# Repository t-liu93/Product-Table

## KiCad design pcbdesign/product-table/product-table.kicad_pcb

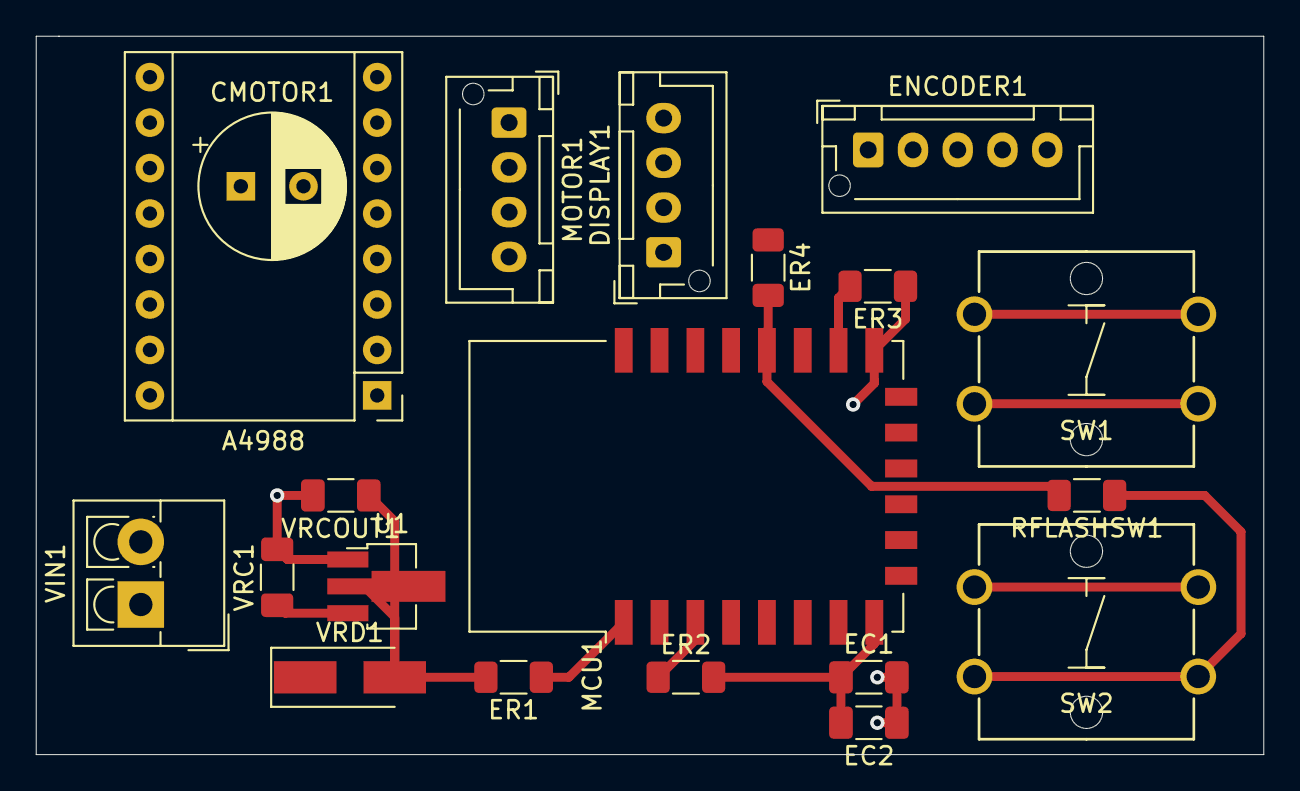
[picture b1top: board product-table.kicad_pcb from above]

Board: 2 copper layers, 68.6 x 40.1 mm, 20 parts (0 on the bottom side), 19 nets.

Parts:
A4988: Pololu_Breakout_A4988; Pololu_Breakout-16_15.2x20.3mm
CMOTOR1: 100uF; CP_Radial_D8.0mm_P3.50mm
DISPLAY1: Conn_01x04; JST_XH_B4B-XH-AM_1x04_P2.50mm_Vertical
EC1: 10uF; C_1206_3216Metric_Pad1.33x1.80mm_HandSolder
EC2: 100nF; C_1206_3216Metric_Pad1.33x1.80mm_HandSolder
ENCODER1: Conn_01x05; JST_XH_B5B-XH-AM_1x05_P2.50mm_Vertical
ER1, ER2, ER3, ER4: 10K; R_1206_3216Metric_Pad1.30x1.75mm_HandSolder
MCU1: ESP-12F; ESP-12E
MOTOR1: Conn_01x04; JST_XH_B4B-XH-AM_1x04_P2.50mm_Vertical
RFLASHSW1: 100; R_1206_3216Metric_Pad1.30x1.75mm_HandSolder
SW1, SW2: Omron-B3F-4055; SW_PUSH_Omron_B3F-4055
U1: LM1117-3.3; SOT-89-3_Handsoldering
VIN1: Terminal; TerminalBlock_4Ucon_1x02_P3.50mm_Vertical
VRC1: 10uF; C_1206_3216Metric_Pad1.33x1.80mm_HandSolder
VRCOUT1: 10uF; C_1206_3216Metric_Pad1.33x1.80mm_HandSolder
VRD1: D_Schottky; D_SMA_Handsoldering

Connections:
+3V3: A4988.2, A4988.10, A4988.11, A4988.12, DISPLAY1.1, EC1.1, EC2.2, ENCODER1.2, ER1.2, ER2.2, ER4.1, MCU1.8, U1.2, VRCOUT1.1, VRD1.2
+12V: A4988.8, CMOTOR1.1, U1.3, VIN1.1, VRC1.1, VRD1.1
/GPIO0: A4988.15, ER4.2, MCU1.18, RFLASHSW1.2
/GPIO2: A4988.16, MCU1.17
/GPIO4: DISPLAY1.4, MCU1.19
/GPIO5: DISPLAY1.3, MCU1.20
/GPIO12: ENCODER1.4, MCU1.6
/GPIO13: ENCODER1.5, MCU1.7
/GPIO14: ENCODER1.3, MCU1.5
/esp8266/EN: ER2.1, MCU1.3
/esp8266/GPIO15: ER3.2, MCU1.16
/esp8266/RST: ER1.1, MCU1.1, SW1.3, SW1.4
GND: A4988.1, A4988.7, A4988.9, CMOTOR1.2, DISPLAY1.2, EC1.2, EC2.1, ENCODER1.1, ER3.1, MCU1.15, SW1.1, SW1.2, SW2.3, SW2.4, U1.1, VIN1.2, VRC1.2, VRCOUT1.2
unnamed: A4988.3, MOTOR1.1
unnamed: A4988.4, MOTOR1.2
unnamed: A4988.5, MOTOR1.3
unnamed: A4988.6, MOTOR1.4
unnamed: A4988.13, A4988.14
unnamed: RFLASHSW1.1, SW2.1, SW2.2

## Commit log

2020-06-04 Initialize submodules
2020-06-04 Initialize Makefile
2020-06-04 Add .gitignore
2020-10-11 Bump Arduino 2.7.4
2020-10-11 Remove submodule to change location
2020-10-11 Add submodule Arduino and makefile
2020-10-11 Add submodule ota
2020-10-11 Add timer class
2020-10-11 Remove
2020-10-11 New sub
2020-10-11 Update purge submodules
2020-10-11 Start with it
2020-10-12 Add u8g2
2020-10-14 Add stepper driver library
2020-10-23 Add submodule
2020-10-23 Add PCB design
2020-10-23 commit pcb
2020-10-23 Bump esp
2020-10-24 Remove cache of backup files
2020-10-24 Remove some no needed files
2020-10-24 Update gitignore with necessary kicad info
2020-10-24 Bump ota
2020-10-24 Remove ota submodule, will be changed by new one
2020-10-24 Update submodule OTA
2020-10-24 Remove two esp lib
2020-10-24 Remove submodules of pcb design
2020-10-24 Add submodules
2020-10-24 Update all
2020-10-24 Add submodule kicad
2020-11-10 Updated pcb design
2020-11-10 Update lib directories
2020-11-10 Update submodules
2020-11-10 Move to src
2020-11-10 Add WifiManager
2020-11-10 Remove old Makefile and switch to Platformio
2020-11-10 Not commit vscode
2020-11-10 Update gitignore
2020-11-10 Update hostname
2020-11-11 Split software and pcbdesign
2020-11-11 Rearrange submodules
2020-11-11 Update gitignore for subsw
2020-11-11 Use main.cpp
2020-11-12 Some updated with tasks
2020-11-12 Initialize ATMega328p version
2020-11-13 Start implmenenting controll of TMC2208
2020-11-14 Remove u8g2 because platformio will add it
2020-11-14 Remove all ESP submodules
